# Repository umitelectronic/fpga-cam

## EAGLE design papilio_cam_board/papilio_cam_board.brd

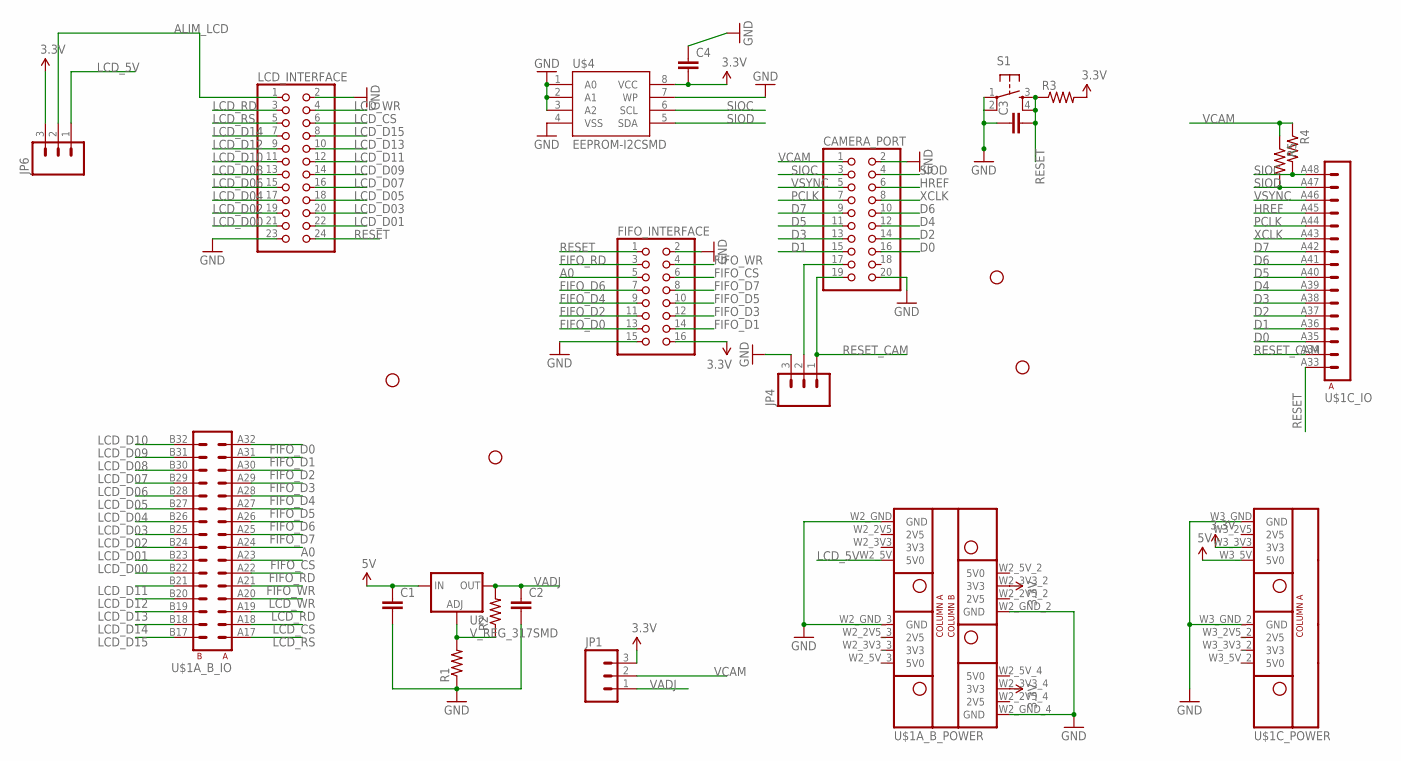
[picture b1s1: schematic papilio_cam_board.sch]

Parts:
C1, C2, C3, C4: CAP0805; 0805
CAMERA_PORT: PINHD-2X10; 2X10
FIFO_INTERFACE: PINHD-2X8; 2X08
JP1, JP4, JP6: M03PTH; 1X03
JP2, JP3, JP5, JP7: STAND-OFF
LCD_INTERFACE: PINHD-2X12; 2X12
LOGO1: BUTTERFLY_LOGO
R1, R2, R3, R4, R5: RESISTOR0805-RES; 0805
S1: TAC_SWITCHSMD; TACTILE_SWITCH_SMD
U2: V_REG_317SMD; SOT223
U$1: MEGAWING_FULL_P1MEGAWING_P1; MEGAWING_FULL_NOHOLES_P1
U$4: EEPROM-I2CSMD; SO08

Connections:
3.3V: C4.2, FIFO_INTERFACE.16, JP1.3, JP6.3, R3.2, U$1.W2_3V3_2 (3V3), U$1.W2_3V3_4 (3V3), U$1.W3_3V3 (3V3), U$4.8 (VCC)
5V: C1.1, U2.3 (IN), U$1.W3_5V (5V0)
A0: FIFO_INTERFACE.5, U$1.A24 (A8)
ALIM_LCD: JP6.2, LCD_INTERFACE.1
D0: CAMERA_PORT.16, U$1.A35 (A3)
D1: CAMERA_PORT.15, U$1.A36 (A4)
D2: CAMERA_PORT.14, U$1.A37 (A5)
D3: CAMERA_PORT.13, U$1.A38 (A6)
D4: CAMERA_PORT.12, U$1.A39 (A7)
D5: CAMERA_PORT.11, U$1.A40 (A8)
D6: CAMERA_PORT.10, U$1.A41 (A9)
D7: CAMERA_PORT.9, U$1.A42 (A10)
FIFO_CS: FIFO_INTERFACE.6, U$1.A23 (A7)
FIFO_D0: FIFO_INTERFACE.13, U$1.A32 (A16)
FIFO_D1: FIFO_INTERFACE.14, U$1.A31 (A15)
FIFO_D2: FIFO_INTERFACE.11, U$1.A30 (A14)
FIFO_D3: FIFO_INTERFACE.12, U$1.A29 (A13)
FIFO_D4: FIFO_INTERFACE.9, U$1.A28 (A12)
FIFO_D5: FIFO_INTERFACE.10, U$1.A27 (A11)
FIFO_D6: FIFO_INTERFACE.7, U$1.A26 (A10)
FIFO_D7: FIFO_INTERFACE.8, U$1.A25 (A9)
FIFO_RD: FIFO_INTERFACE.3, U$1.A22 (A6)
FIFO_WR: FIFO_INTERFACE.4, U$1.A21 (A5)
GND: C1.2, C2.2, C3.1, C4.1, CAMERA_PORT.2, CAMERA_PORT.20, FIFO_INTERFACE.2, FIFO_INTERFACE.15, JP4.3, LCD_INTERFACE.2, LCD_INTERFACE.23, R1.1, S1.1, S1.2, U$1.W2_GND (GND), U$1.W2_GND_2 (GND), U$1.W2_GND_3 (GND), U$1.W2_GND_4 (GND), U$1.W3_GND (GND), U$1.W3_GND_2 (GND), U$4.1 (A0), U$4.2 (A1), U$4.3 (A2), U$4.4 (VSS), U$4.7 (WP)
HREF: CAMERA_PORT.6, U$1.A45 (A13)
LCD_5V: JP6.1, U$1.W2_5V (5V0)
LCD_CS: LCD_INTERFACE.6, U$1.A18 (A2)
LCD_D00: LCD_INTERFACE.21, U$1.B22 (B6)
LCD_D01: LCD_INTERFACE.22, U$1.B23 (B7)
LCD_D02: LCD_INTERFACE.19, U$1.B24 (B8)
LCD_D03: LCD_INTERFACE.20, U$1.B25 (B9)
LCD_D04: LCD_INTERFACE.17, U$1.B26 (B10)
LCD_D05: LCD_INTERFACE.18, U$1.B27 (B11)
LCD_D06: LCD_INTERFACE.15, U$1.B28 (B12)
LCD_D07: LCD_INTERFACE.16, U$1.B29 (B13)
LCD_D08: LCD_INTERFACE.13, U$1.B30 (B14)
LCD_D09: LCD_INTERFACE.14, U$1.B31 (B15)
LCD_D10: LCD_INTERFACE.11, U$1.B32 (B16)
LCD_D11: LCD_INTERFACE.12, U$1.B21 (B5)
LCD_D12: LCD_INTERFACE.9, U$1.B20 (B4)
LCD_D13: LCD_INTERFACE.10, U$1.B19 (B3)
LCD_D14: LCD_INTERFACE.7, U$1.B18 (B2)
LCD_D15: LCD_INTERFACE.8, U$1.B17 (B1)
LCD_RD: LCD_INTERFACE.3, U$1.A19 (A3)
LCD_RS: LCD_INTERFACE.5, U$1.A17 (A1)
LCD_WR: LCD_INTERFACE.4, U$1.A20 (A4)
unnamed: R1.2, R2.1, U2.1 (ADJ)
unnamed: CAMERA_PORT.17, JP4.2
PCLK: CAMERA_PORT.7, U$1.A44 (A12)
RESET: C3.2, FIFO_INTERFACE.1, LCD_INTERFACE.24, R3.1, S1.3, S1.4, U$1.A33 (A1)
RESET_CAM: CAMERA_PORT.19, JP4.1, U$1.A34 (A2)
SIOC: CAMERA_PORT.3, R4.2, U$1.A48 (A16), U$4.6 (SCL)
SIOD: CAMERA_PORT.4, R5.2, U$1.A47 (A15), U$4.5 (SDA)
VADJ: C2.1, JP1.1, R2.2, U2.2 (OUT)
VCAM: CAMERA_PORT.1, JP1.2, R4.1, R5.1
VSYNC: CAMERA_PORT.5, U$1.A46 (A14)
XCLK: CAMERA_PORT.8, U$1.A43 (A11)

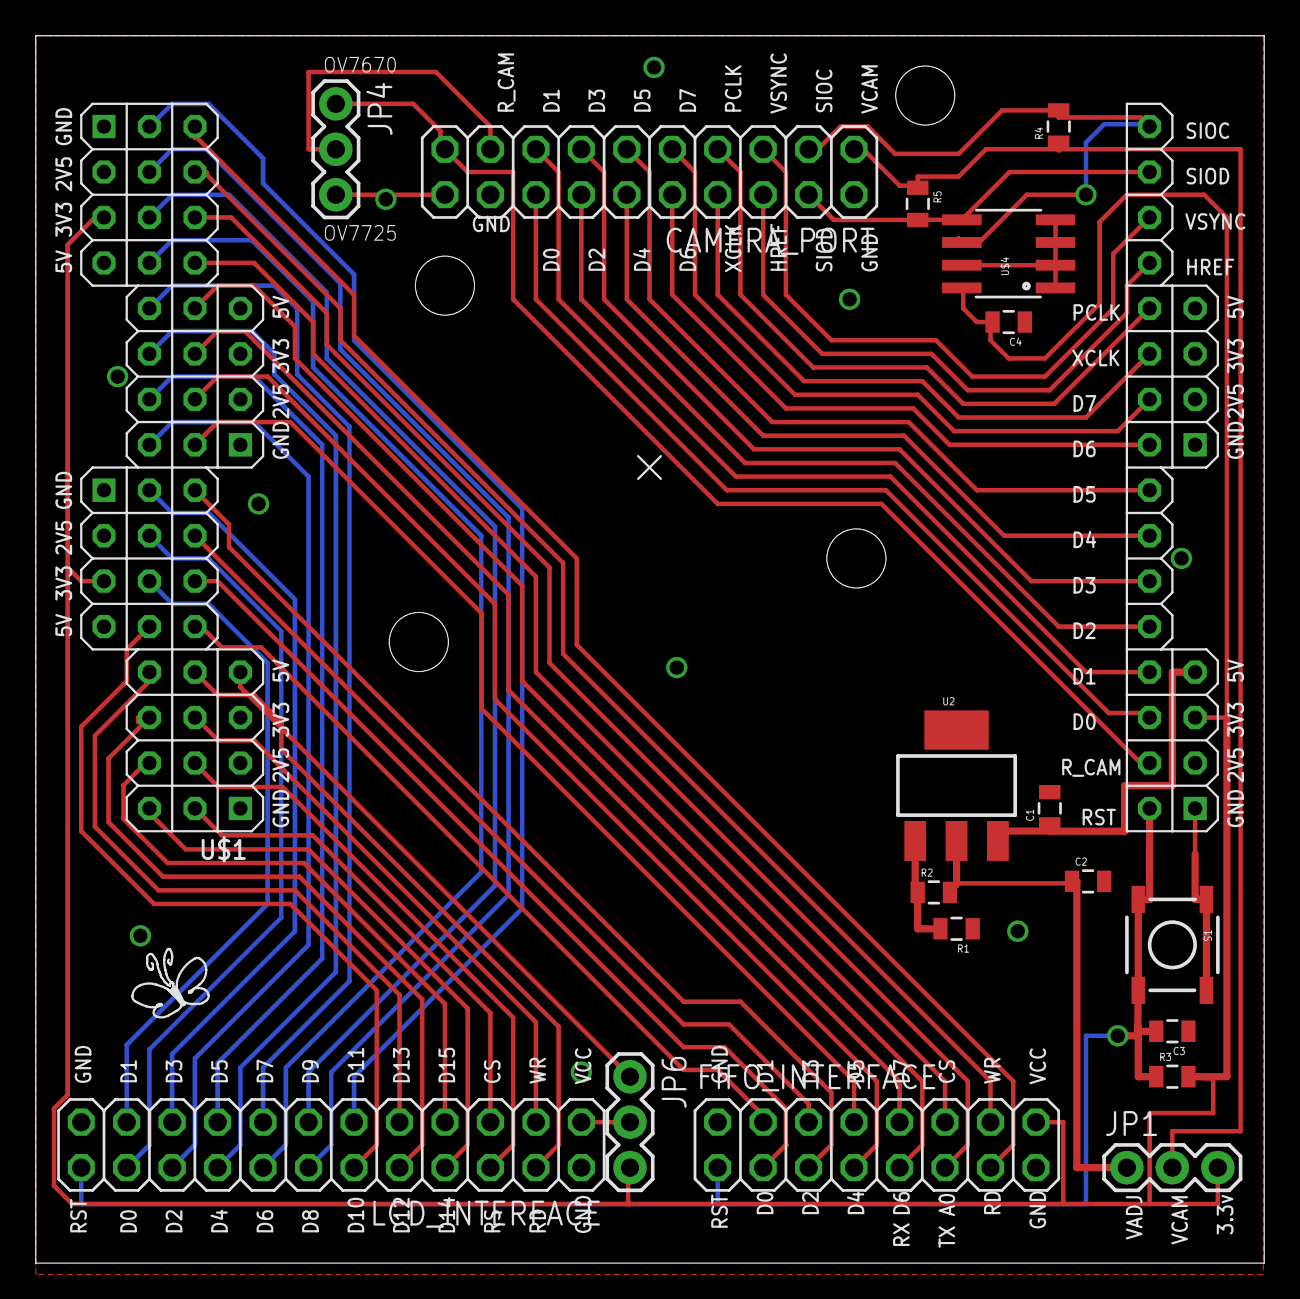
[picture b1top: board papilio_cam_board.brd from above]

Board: 2 copper layers, 68.6 x 68.6 mm, 24 parts (0 on the bottom side), 57 nets.

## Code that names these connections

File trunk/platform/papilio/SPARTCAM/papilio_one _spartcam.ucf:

# Papilio User Constraints File

# Main board wing pin [] to FPGA pin Pxx map
# -------C-------    -------B-------    -------A-------
# [GND] [C00] P91    [GND] [B00] P85    P86 [A15]
# [2V5] [C01] P92    [2V5] [B01] P83    P84 [A14]
# [3V3] [C02] P94    [3V3] [B02] P78    P79 [A13]
# [5V0] [C03] P95    [5V0] [B03] P71    P70 [A12]
#       [C04] P98          [B04] P68    P67 [A11] [5V0]
#       [C05] P2           [B05] P66    P65 [A10] [3V3]
#       [C06] P3           [B06] P63    P62 [A09] [2V5]
#       [C07] P4           [B07] P61    P60 [A08] [GND]
# [GND] [C08] P5     [GND] [B08] P58    P57 [A07]
# [2V5] [C09] P9     [2V5] [B09] P54    P53 [A06]
# [3V3] [C10] P10    [3V3] [B10] P41    P40 [A05]
# [5V0] [C11] P11    [5V0] [B11] P36    P35 [A04]
#       [C12] P12          [B12] P34    P33 [A03] [5V0]
#       [C13] P15          [B13] P32    P26 [A02] [3V3]
#       [C14] P16          [B14] P25    P23 [A01] [2V5]
#       [C15] P17          [B15] P22    P18 [A00] [GND]

# Wing pin to FPGA pin map

# Pin AH   BH   CH     VGA    Audio   MicroSD  PS2    Button
# 15  P86  P22  P17    RED    A1L     -        -      PB1
# 14  P84  P25  P16    GRN    A1S     -        -      LED1
# 13  P79  P32  P15    -      A1R     D2       -      PB2
# 12  P70  P34  P12    -      -       CS       -      LED2
# 11  P67  P36  P11    -      -       SI       DAT2   PB3
# 10  P65  P41  P10    BLU    A2L     SCK      CLK2   LED3
# 09  P62  P54  P9     HS     A2S     SO       DAT1   PB4
# 08  P60  P58  P5     VS     A2R     D1       CLK1   LED4

# Pin AL   BL   CL     VGA8   Audio   MicroSD  PS2    Button
# 07  P57  P61  P4     RED    A1L     -        -      PB1
# 06  P53  P63  P3     GRN    A1S     -        -      LED1
# 05  P40  P66  P2     -      A1R     D2       -      PB2
# 04  P35  P68  P98    -      -       CS       -      LED2
# 03  P33  P71  P95    -      -       SI       DAT2   PB3
# 02  P26  P78  P94    BLU    A2L     SCK      CLK2   LED3
# 01  P23  P83  P92    HS     A2S     SO       DAT1   PB4
# 00  P18  P85  P91    VS     A2R     D1       ClK1   LED4

# Example 1
# Say you have a button board BPW5007 plugged into wing AL look at a pin in
# the "Button" column, say LED4 then across to column AL and you can see it
# corresponds to FPGA pin P18, if the same board was plugged into BH then
# LED4 would be P58

# Example 2
# If you have a VGA board BPW5017 plugged into wing CH, then look at a pin
# under the VGA8 column, say BLU and across to column CH and you find that
# BLU is FPGA pin P10, if the same VGA board was plugged into wing AH then
# BLU would be FPGA pin P65

# Once you find the FPGA pin, go to the NET definition below and uncomment
# the respective line. You may rename the NET from WingX_Ynn to the name you
# use in your design

###########################################################
# UCF File starts here, uncomment lines below as required #
###########################################################

#CONFIG PART = XC3S500E-VQ100-4 ;
CONFIG PART = XC3S250E-VQ100-4 ;

#NET I_CLK_REF  TNM_NET = clk_ref_grp;
#TIMESPEC TS01 = PERIOD : clk_ref_grp : 31.25ns : PRIORITY 1;   # 32.00 MHz

TIMESPEC TS11 = FROM:PADS:TO:FFS : 30 ns;
TIMESPEC TS12 = FROM:FFS:TO:PADS : 5 ns;

NET CLK							LOC = "P89"  | IOSTANDARD = LVCMOS25 | PERIOD = 31.25ns; # 32.00 MHz oscillator

#NET JTAG_TMS					LOC = "P75"  | IOSTANDARD = LVTTL | DRIVE = 8 | SLEW = FAST ;
#NET JTAG_TCK					LOC = "P77"  | IOSTANDARD = LVTTL | DRIVE = 8 | SLEW = FAST ;
#NET JTAG_TDI					LOC = "P100" | IOSTANDARD = LVTTL | DRIVE = 8 | SLEW = FAST ;
#NET JTAG_TDO					LOC = "P76"  | IOSTANDARD = LVTTL | DRIVE = 8 | SLEW = FAST ;

NET RXD							LOC = "P88"  | IOSTANDARD = LVTTL | DRIVE = 8 | SLEW = SLOW ;
NET TXD							LOC = "P90"  | IOSTANDARD = LVTTL | DRIVE = 8 | SLEW = SLOW ;

#NET FLASH_CS					LOC = "P24"  | IOSTANDARD = LVTTL | DRIVE = 8 | SLEW = FAST ;
#NET FLASH_CK					LOC = "P50"  | IOSTANDARD = LVTTL | DRIVE = 8 | SLEW = FAST ;
#NET FLASH_SI					LOC = "P27"  | IOSTANDARD = LVTTL | DRIVE = 8 | SLEW = FAST ;
#NET FLASH_SO					LOC = "P44"  | IOSTANDARD = LVTTL | DRIVE = 8 | SLEW = FAST | PULLUP;

NET LCD_DATA<14>				LOC = "P86"  | IOSTANDARD = LVTTL | DRIVE = 8 | SLEW = SLOW  ; 
NET LCD_DATA<15>				LOC = "P84"  | IOSTANDARD = LVTTL | DRIVE = 8 | SLEW = SLOW  ;
NET LCD_DATA<12>				LOC = "P79"  | IOSTANDARD = LVTTL | DRIVE = 8 | SLEW = SLOW  ;
NET LCD_DATA<13>				LOC = "P70"  | IOSTANDARD = LVTTL | DRIVE = 8 | SLEW = SLOW  ; 
NET LCD_DATA<10>				LOC = "P67"  | IOSTANDARD = LVTTL | DRIVE = 8 | SLEW = SLOW  ; 
NET LCD_DATA<1>				LOC = "P65"  | IOSTANDARD = LVTTL | DRIVE = 8 | SLEW = SLOW  ; 
NET LCD_DATA<0>				LOC = "P62"  | IOSTANDARD = LVTTL | DRIVE = 8 | SLEW = SLOW  ; 
NET LCD_DATA<3>				LOC = "P60"  | IOSTANDARD = LVTTL | DRIVE = 8 | SLEW = SLOW  ; 
NET LCD_DATA<2>				LOC = "P57"  | IOSTANDARD = LVTTL | DRIVE = 8 | SLEW = SLOW  ;
NET LCD_DATA<5>				LOC = "P53"  | IOSTANDARD = LVTTL | DRIVE = 8 | SLEW = SLOW  ; 
NET LCD_DATA<4>				LOC = "P40"  | IOSTANDARD = LVTTL | DRIVE = 8 | SLEW = SLOW  ; 
NET LCD_DATA<7>				LOC = "P35"  | IOSTANDARD = LVTTL | DRIVE = 8 | SLEW = SLOW  ; 
NET LCD_DATA<6>				LOC = "P33"  | IOSTANDARD = LVTTL | DRIVE = 8 | SLEW = SLOW  ; 
NET LCD_DATA<9>				LOC = "P26"  | IOSTANDARD = LVTTL | DRIVE = 8 | SLEW = SLOW  ; 
NET LCD_DATA<8>				LOC = "P23"  | IOSTANDARD = LVTTL | DRIVE = 8 | SLEW = SLOW  ; 
NET LCD_DATA<11>				LOC = "P18"  | IOSTANDARD = LVTTL | DRIVE = 8 | SLEW = SLOW  ; 

NET LCD_CS						LOC = "P85"  | IOSTANDARD = LVTTL | DRIVE = 8 | SLEW = FAST | PULLUP | TNM_NET = TS12; 
NET LCD_RS						LOC = "P83"  | IOSTANDARD = LVTTL | DRIVE = 8 | SLEW = FAST | PULLUP | TNM_NET = TS12; 
NET LCD_WR						LOC = "P78"  | IOSTANDARD = LVTTL | DRIVE = 8 | SLEW = FAST | PULLUP | TNM_NET = TS12; 
NET LCD_RD						LOC = "P71"  | IOSTANDARD = LVTTL | DRIVE = 8 | SLEW = FAST | PULLUP | TNM_NET = TS12; 
NET FIFO_DATA<1>				LOC = "P68"  | IOSTANDARD = LVTTL | DRIVE = 8 | SLEW = SLOW | PULLUP; 
NET FIFO_DATA<0>				LOC = "P66"  | IOSTANDARD = LVTTL | DRIVE = 8 | SLEW = SLOW | PULLUP; 
NET FIFO_DATA<3>				LOC = "P63"  | IOSTANDARD = LVTTL | DRIVE = 8 | SLEW = SLOW | PULLUP; 
NET FIFO_DATA<2>				LOC = "P61"  | IOSTANDARD = LVTTL | DRIVE = 8 | SLEW = SLOW | PULLUP; 
NET FIFO_DATA<5>				LOC = "P58"  | IOSTANDARD = LVTTL | DRIVE = 8 | SLEW = SLOW | PULLUP;
NET FIFO_DATA<4>				LOC = "P54"  | IOSTANDARD = LVTTL | DRIVE = 8 | SLEW = SLOW | PULLUP; 
NET FIFO_DATA<7>				LOC = "P41"  | IOSTANDARD = LVTTL | DRIVE = 8 | SLEW = SLOW | PULLUP; 
NET FIFO_DATA<6>				LOC = "P36"  | IOSTANDARD = LVTTL | DRIVE = 8 | SLEW = SLOW | PULLUP; 
NET FIFO_CS						LOC = "P34"  | IOSTANDARD = LVTTL | DRIVE = 8 | SLEW = SLOW | PULLUP;
NET FIFO_A0						LOC = "P32"  | IOSTANDARD = LVTTL | DRIVE = 8 | SLEW = SLOW | PULLUP;
NET FIFO_WR						LOC = "P25"  | IOSTANDARD = LVTTL | DRIVE = 8 | SLEW = SLOW | PULLUP;
NET FIFO_RD						LOC = "P22"  | IOSTANDARD = LVTTL | DRIVE = 8 | SLEW = SLOW | PULLUP; 

NET ARAZB						LOC = "P91"  | IOSTANDARD = LVTTL | DRIVE = 8 | SLEW = SLOW ; 
NET CAM_RESET					LOC = "P92"  | IOSTANDARD = LVTTL | DRIVE = 8 | SLEW = SLOW ; 
NET CAM_DATA<0>				LOC = "P94"  | IOSTANDARD = LVTTL | DRIVE = 8 | SLEW = SLOW ; 
NET CAM_DATA<1>				LOC = "P95"  | IOSTANDARD = LVTTL | DRIVE = 8 | SLEW = SLOW ; 
NET CAM_DATA<2>				LOC = "P98"  | IOSTANDARD = LVTTL | DRIVE = 8 | SLEW = SLOW ; 
NET CAM_DATA<3>				LOC = "P2"   | IOSTANDARD = LVTTL | DRIVE = 8 | SLEW = SLOW ; 
NET CAM_DATA<4>				LOC = "P3"   | IOSTANDARD = LVTTL | DRIVE = 8 | SLEW = SLOW ; 
NET CAM_DATA<5>				LOC = "P4"   | IOSTANDARD = LVTTL | DRIVE = 8 | SLEW = SLOW ; 
NET CAM_DATA<6>				LOC = "P5"   | IOSTANDARD = LVTTL | DRIVE = 8 | SLEW = SLOW ; 
NET CAM_DATA<7>				LOC = "P9"   | IOSTANDARD = LVTTL | DRIVE = 8 | SLEW = SLOW ; 
NET CAM_XCLK					LOC = "P10"  | IOSTANDARD = LVTTL | DRIVE = 8 | SLEW = FAST | PERIOD = 41.6ns; # 24Mhz
NET CAM_PCLK					LOC = "P11"  | IOSTANDARD = LVTTL | DRIVE = 8 | SLEW = FAST | TNM_NET = TS11; 
NET CAM_HREF					LOC = "P12"  | IOSTANDARD = LVTTL | DRIVE = 8 | SLEW = FAST | TNM_NET = TS11; 
NET CAM_VSYNC					LOC = "P15"  | IOSTANDARD = LVTTL | DRIVE = 8 | SLEW = FAST | TNM_NET = TS11; 
NET CAM_SIOD					LOC = "P16"  | IOSTANDARD = LVTTL | DRIVE = 8 | SLEW = SLOW | PULLUP; 
NET CAM_SIOC					LOC = "P17"  | IOSTANDARD = LVTTL | DRIVE = 8 | SLEW = SLOW | PULLUP; 

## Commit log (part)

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2012-07-25 Updating LCD controller to work with SSD1289. Needs to be merged with the other LCD controller using generics.
2012-07-26 Updating DCM and reset handling on LCD and SOBEL designs
2012-07-27 Working on Database-based configuration generator
2012-07-27 Adding HDL data parser and working on management GUI
2012-07-31 removing french references
2012-09-06 improving pipeline elements to get them running at pixel clock speed instead of system clock speed.
2012-09-27 addinf fx2 communication interface, simplyfying camera interface
2012-09-28 fx2 firmware for fpga communication
2012-10-02 getting ov7725 to work at 30fps (15fps, 50 fps, 75 fps also works)
2012-10-02 ov7725 example
2012-10-04 adding generic components and improving design
2012-10-04 adding viewer relying on fx2 communication
2012-10-04 readme file with link to resources
2012-10-04 working on simple brief method for pattern matching
2012-10-09 generic hamming distance computation for powers of two
2012-10-09 removing unused files
2012-10-09 working on active search
2012-10-11 working on harris computation
2012-10-12 small bug in block_3x3 and harris closed to be done
2012-10-16 harris is still a work in progress as window get shift by its size when it should on ly be shifted by one ...
2012-10-16 still debugging the degraded harris (works nice)
2012-10-17 harris downalsampled is now working
2012-10-18 harris no downsampling is working !
2012-10-23 now using small memory footprint of harris only 4 BRAMS for HARRIS and should work on VGA picture on QVGA@120fps
2012-10-23 working on image tesselation for feature extraction
2012-10-25 harris tesselation now works ! Module output best harris values in window of selected size
2012-12-07 reconstructed missing package file. Still missing the HARRIS_LINE_ACC_SMALL ...
2012-12-10 Added spi2wishbone and mark1_master_ucf
2012-12-14 deleting faulty folder (naming problem)
2012-12-14 fixing naming problem in repository
2012-12-14 added configuration for ssd1289 based LCD
2012-12-14 folder for mark1 platform
2012-12-14 adding demo files (work in progress)
2012-12-14 changing packages organization
2012-12-16 loopback project to test with beaglebone
2012-12-17 Fixed ucf syntax errors
2012-12-17 refactoring of the repository in progress
2012-12-17 still on refactoring repo structure
2012-12-18 small changes
2012-12-18 small changes to allow multiple peripheral on one bus
2012-12-18 changes on demo, now using ISE 14.1
2012-12-18 adding software files to the repository
2012-12-18 adding files fomr demo
2012-12-18 update on project and README file added
2012-12-18 updateon project and readme file
2012-12-18 added testbenc for main project
2012-12-18 small correction to avoid bus conflicts et doxygen documentation added (still a lot to do ..)
2012-12-19 improving testbench
2012-12-19 small changes to ucf and main file
2012-12-19 GPMC_CLK cannot be used as FPGA main clock as its only active on bus access. Switching back to using FPGA_OSC. One should use a DCM to generate a 100Mhz clock.
2012-12-21 added pll for clock generation
2012-12-21 none
2012-12-27 Added UCF for Logi-Bone RA1
2012-12-28 trying to remove pll
2013-01-03 small modification on WEIN and BEON (changed to WEN and BE0N)
2013-01-03 logibone demo (almost) ready to be tested
2013-01-03 working logicape demo
2013-01-03 changed to configure prog, init, done pins of the fpga
2013-01-03 change to improve bus frequency
2013-01-03 change to demo to work ad faster clock speed
2013-01-03 added clock_gen to generate 120Mhz and 24Mhz camera clock
2013-01-04 splitting camera into config and interface. Correcting package bugs
2013-01-04 new demo with camera and working interface to beaglebone
2013-01-05 mjpeg streamer plugin working, still need improvement
2013-01-05 small change to reflect switch to logibone
2013-01-10 adde new fifo to pixel block to allow to emulat camera signal from fifo output
2013-01-11 New demo for sobel filtering from beaglebone image
2013-01-11 new fifo2pixel working
2013-01-11 changing stuff
2013-01-12 cleaning up software and working on image processing demo
2013-01-13 new logibone demo and mark1 demo
2013-01-13 other files for demo
2013-01-13 vhdl files for demo
2013-01-13 changes to improve synthesis
2013-01-15 new canny demo working still some work to get fifo working properly
2013-01-15 canny added to demos
2013-01-15 modifed grabber code for faster speed
2013-01-16 edma fifo module to get fast communication speeds
2013-01-17 figures for tutorial on hardware sobel filter
2013-01-17 modifying document
2013-01-17 adding grad image
2013-01-17 added sobel filetred image
2013-01-20 new cahnges in edma fifo mode, still needs testing
2013-01-20 new change
2013-01-21 new demo with edma
2013-01-22 new sobel filter pipelined at the pixel level
2013-01-22 new demo on the way
2013-01-22 minor change to get the pipeline sobel filter to work
2013-01-22 working oon hsync generation
2013-01-23 small change on signal delay
2013-01-23 samll changes to accomodate new clock management strategy
2013-01-23 minor change and new component for bridging clock domains
2013-01-23 new component to bridge clock domains
2013-01-24 new mining project in the work
2013-01-24 minor changes
2013-01-24 it seems to synthesize ...
2013-01-25 added clock generation and errors corrected
2013-01-25 working on a Python interface for the logibone
2013-01-25 minor change to allw the script to detect module presence
2013-01-28 major changes to project
2013-01-28 change to addr mux to reflect use of config pins
2013-01-29 new features added, still a work in progress.
2013-01-30 miner is now workin, still need to get the software part working
2013-01-30 changes on memory interface and new addressable latches peripheral
2013-02-01 new project for bit coin mining
2013-02-01 small modification to logibone project. Now working !
2013-02-02 new serial loader !
2013-02-02 deleting stuff
2013-02-03 modification to serial loader
2013-02-03 small modification to loader, now goes faster
2013-02-03 loader is now faster (still not fast ...)
2013-02-03 updated loader to get faster configuration time
2013-02-04 added timing functions to loader
2013-02-04 small change to the make_demo script
2013-02-04 improving mining architecture to get rid off fifo
2013-02-15 added serial loader and error corrected in grabber program
2013-02-15 image to show the architecture in the FPGA
2013-02-15 new make demo script
2013-02-15 updated job interval time
2013-02-15 cleaning up the repo
2013-02-15 cleaning up things
2013-02-15 cleaning ...
2013-02-15 nothing important
2013-02-15 removing unused stuff
2013-02-15 clean ! clean ! clean !
2013-02-15 clean ...
2013-02-15 adding what i just cleaned ...
2013-02-15 relocating ucf file in correponding platform folder
2013-02-15 relocating stuff
2013-02-18 reconstructing missing files after stolen laptop
2013-02-25 trying to get the mark1 programmnig code working ..
2013-02-25 updated version
2013-02-25 working !
2013-02-25 relocating loader code
2013-02-25 adding auto-detect of logi board
2013-02-25 new project for mark1
2013-02-25 updated mux settings
2013-02-25 new mining demo with mark1 support
2013-02-25 updated to auto-detect distro (Angstrom or Ubuntu)
2013-02-27 working hard to the way to SLAM!
2013-03-01 imporving things
2013-03-01 still working on SLAM implementation, not far ...
2013-03-04 small change in camera project
2013-03-04 tracking project on the way
2013-03-05 bug corrected
2013-03-05 fixing missing files
2013-03-07 major chnage to tracking porject and library
2013-03-08 some modification and improvements for correlation
2013-03-08 improving tracking project
2013-03-09 improving for streaming demo, still a bit to do ...
2013-03-10 trying to solve synchronization issues with mjpeg streamer
2013-03-11 working on getting interrupts to work
2013-03-11 working on getting interrupts between FPGA and beaglebone to work
2013-03-11 working on a interrupt manager to generate interrupts to the beaglebone
2013-03-17 improving blob tracking
2013-03-18 improving blob detection, demo soon to come
2013-03-18 updating lcd project to reflect library changes
2013-03-18 updating files for LCD project
2013-03-18 project update
2013-03-18 new tracking project !
2013-03-18 correcting dependencies
2013-03-18 improving detection example
2013-03-19 minor improvement to take vsync into account
2013-03-20 trying to refactore svn structure
2013-03-20 improving fifo lib to automatically switch to module-less fifo
2013-03-20 improving plugin to get rid of kernel module
2013-03-20 improving fifo use
2013-03-20 trying to improve mjpeg-streamer plugin ...
2013-03-21 major change to fifo, to support more than one fifo
2013-03-21 great improvement now works reliabily
2013-03-21 addr interface fixed to support byte write access (the good way ...), projects updated
2013-03-21 testing blob tracking
2013-03-22 still trying to improve the tracking
2013-03-22 improving lib for direct memory access (still user space)
2013-04-05 adding author to file
2013-04-06 updated to keep old behavior in the file
2013-04-06 forgot to include xco should fix project
2013-04-07 gpmc support not stable anymore
2013-04-07 gpmc support not stable, byte access is a problem
2013-04-16 forgot this commit
2015-12-13 Migrating wiki contents from Google Code

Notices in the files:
parts and their libraries:
SparkFun: Licensing: CC v3.0 Share-Alike You are welcome to use this library for commercial purposes.
